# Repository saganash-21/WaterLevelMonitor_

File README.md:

# 💧 Arduino-Based Water Level Monitoring for a Horizontal Cylindrical Tank

## 👨‍💻 Author
**Jeremy Ndirangu**

---

## 🧭 Overview
This project implements a **real-time water level monitoring system** for a **horizontally oriented cylindrical tank** using Arduino.  
It combines **geometry**, **embedded systems**, and **PCB design** to calculate water volume precisely and indicate tank levels through LEDs and optional LCD output.

---

## ✨ Features
- Simulates analog water level sensor using a **3296 trimpot (potentiometer)**  
- Calculates **water height and volume** using **circular segment geometry**  
- LED indicators for **Empty**, **Refill**, and **Full** water levels  
- Optional **16x2 LCD Display (I2C)** for live monitoring *(Serial Monitor used for testing)*  
- Custom **PCB design** created with **Eagle CAD**  
- Mathematical derivation included for accurate calibration

---

## 🧱 Folder Structure
```
├── README.md # This file
├── Arduino/ # Arduino source code
├── Schematics/ # Eagle CAD schematic and PCB layout
├── Images/ # Test setup, PCB, and Serial Monitor screenshots
├── Math/ # Mathematical derivations and calculations
├── Documentation/ # Full project report (PDF)
└── LICENSE # MIT License
```

---

## ⚙️ Hardware Used
| Component | Description |
| :--------- | :----------- |
| **Arduino Uno** | Main microcontroller board |
| **3296 Multi-turn Potentiometer** | Simulates analog water level sensor (0–5 V) |
| **LEDs (Red, Yellow, Green)** | Level indicators |
| **Resistors (220Ω)** | Current limiters for LEDs |
| **16x2 LCD Display (I2C)** | Optional live display |
| **Custom PCB** | Designed in Eagle CAD for compactness |

---

## 🔌 System Functionality
1. **Reads** analog voltage from the potentiometer (simulated sensor).  
2. **Maps** voltage to corresponding water height in the cylindrical tank.  
3. **Calculates** cross-sectional area using **circular segment geometry**.  
4. **Computes volume** (in liters) using the segment area and tank length.  
5. **Displays** computed volume on the **Serial Monitor** (or LCD).  
6. **Activates LEDs** to indicate tank status:
   - 🔴 **Empty** (≤ 1000 L)  
   - 🟡 **Refill** (1000 L < volume < 2000 L)  
   - 🟢 **Full** (≥ 4500 L)

---

## 📐 Mathematical Model

For a horizontally laid cylindrical tank:

- **Segment Area:**
  \[
  A = r^2 \cos^{-1}\left(\frac{r - h}{r}\right) - (r - h)\sqrt{2rh - h^2}
  \]

- **Volume:**
  \[
  V = A \times L
  \]

- **Conversion:**
  \[
  1\,\text{cm}^3 = 0.001\,\text{L}
  \]

📘 Detailed derivations available in  
[`Math/Calculations.pdf`](./Math/Calculations.pdf)

---

## 🧪 Testing & Results

### ✅ Serial Monitor Output

### 🧩 Schematic (Eagle CAD)
[`Circuit Schematic`](Schematics/Water_level_schematic_pdf.pdf
)

### ⚙️ Custom PCB Layout

**Observed Results:**
- Real-time volume displayed accurately on Serial Monitor.  
- LEDs switched correctly at threshold volumes:
  - **Red:** ≤ 1000 L  
  - **Yellow:** between 1000 L and 2000 L  
  - **Green:** ≥ 4500 L  
- LCD output provisioned (not tested on hardware).  

---

## 🧾 Documentation
Full detailed report available in  
[`Documentation/Water_Tank_Arduino_Report.pdf`](./Documentation/Water_Tank_Arduino_Report.pdf)

---

## 🪪 License
This project is licensed under the [MIT License](./LICENSE).  
You are free to use, modify, and distribute it.

---

### 🛠️ Designed with Engineering Precision and Practical Application in Mind

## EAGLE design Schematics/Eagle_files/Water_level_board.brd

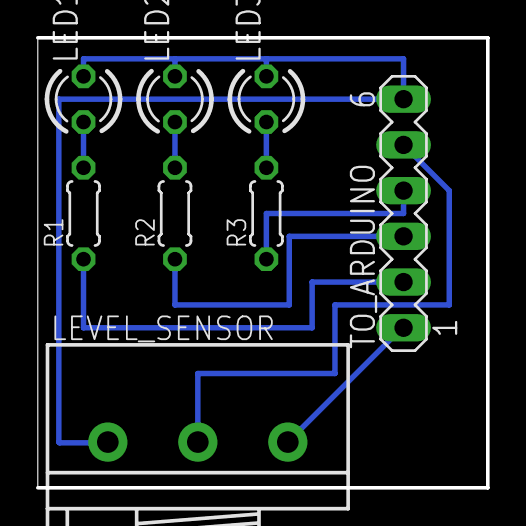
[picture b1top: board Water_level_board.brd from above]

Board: 2 copper layers, 25.0 x 25.0 mm, 8 parts (0 on the bottom side), 9 nets.

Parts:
LED1, LED2, LED3: LED3MM
LEVEL_SENSOR: 3RP/1610N
R1, R2, R3: 0204/5
TO_ARDUINO: MA06-1

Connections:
unnamed: R2.1, TO_ARDUINO.3
unnamed: LEVEL_SENSOR.2, TO_ARDUINO.5
unnamed: R3.1, TO_ARDUINO.4
unnamed: LED1.A, R1.2
unnamed: LED2.A, R2.2
unnamed: R1.1, TO_ARDUINO.2
unnamed: LEVEL_SENSOR.3, TO_ARDUINO.1
unnamed: LED3.A, R3.2
unnamed: LED1.K, LED2.K, LED3.K, LEVEL_SENSOR.1, TO_ARDUINO.6

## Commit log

2025-11-03 Rename README.txt to README.md
